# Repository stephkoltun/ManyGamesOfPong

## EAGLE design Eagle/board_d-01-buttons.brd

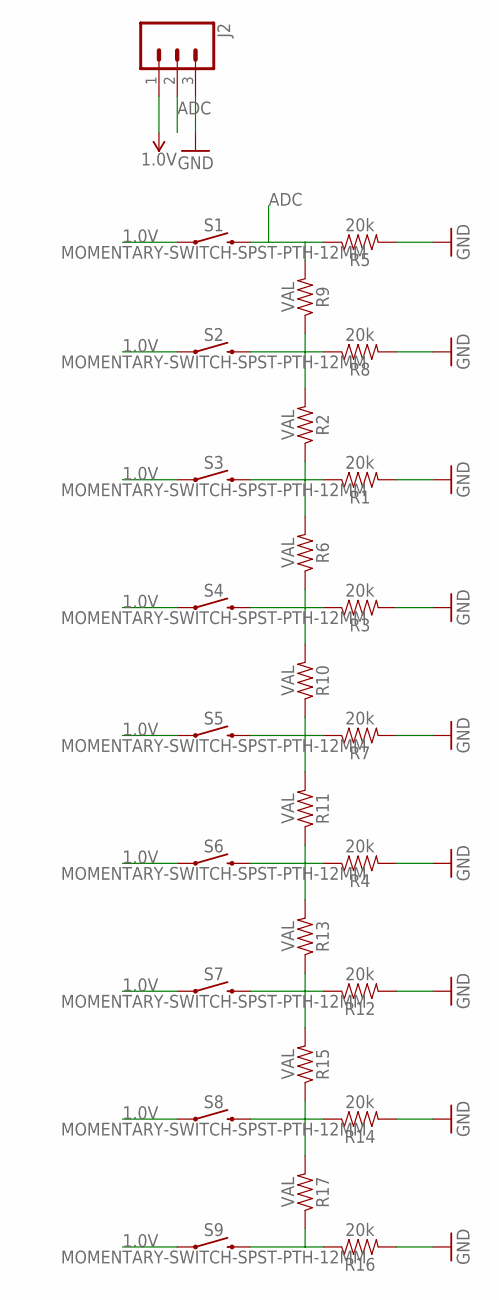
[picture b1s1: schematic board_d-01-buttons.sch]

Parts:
J2: CONN_03LOCK_LONGPADS; 1X03_LOCK_LONGPADS
R1, R3, R4, R5, R7, R8, R12, R14, R16: 20k; AXIAL-0.3
R2, R6, R9, R10, R11, R13, R15, R17: VAL; AXIAL-0.3
S1, S2, S3, S4, S5, S6, S7, S8, S9: MOMENTARY-SWITCH-SPST-PTH-12MM; TACTILE_SWITCH_PTH_12MM

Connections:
1.0V: J2.1, S1.1, S2.1, S3.1, S4.1, S5.1, S6.1, S7.1, S8.1, S9.1
ADC: J2.2, R5.P$1 (1), R9.P$2 (2), S1.3 (2)
GND: J2.3, R1.P$2 (2), R3.P$2 (2), R4.P$2 (2), R5.P$2 (2), R7.P$2 (2), R8.P$2 (2), R12.P$2 (2), R14.P$2 (2), R16.P$2 (2)
unnamed: R1.P$1 (1), R2.P$1 (1), R6.P$2 (2), S3.3 (2)
unnamed: R3.P$1 (1), R6.P$1 (1), R10.P$2 (2), S4.3 (2)
unnamed: R7.P$1 (1), R10.P$1 (1), R11.P$2 (2), S5.3 (2)
unnamed: R4.P$1 (1), R11.P$1 (1), R13.P$2 (2), S6.3 (2)
unnamed: R2.P$2 (2), R8.P$1 (1), R9.P$1 (1), S2.3 (2)
unnamed: R12.P$1 (1), R13.P$1 (1), R15.P$2 (2), S7.3 (2)
unnamed: R14.P$1 (1), R15.P$1 (1), R17.P$2 (2), S8.3 (2)
unnamed: R16.P$1 (1), R17.P$1 (1), S9.3 (2)

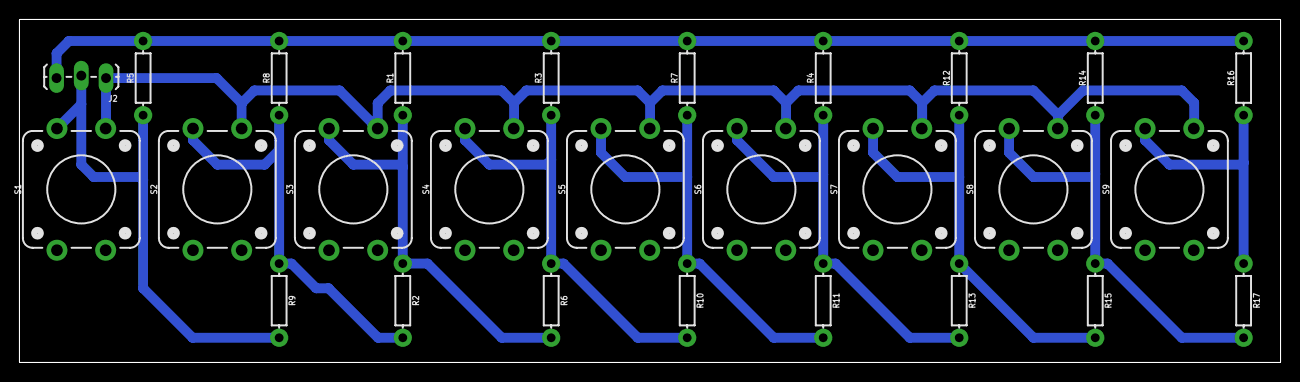
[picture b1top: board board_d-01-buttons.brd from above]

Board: 2 copper layers, 129.5 x 35.2 mm, 27 parts (0 on the bottom side), 11 nets.

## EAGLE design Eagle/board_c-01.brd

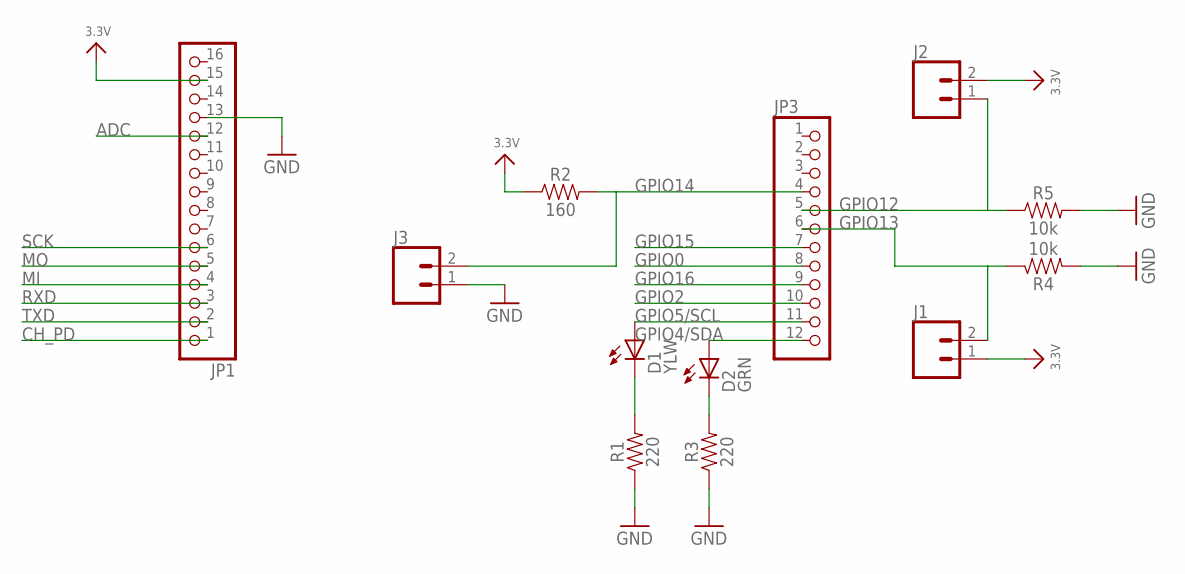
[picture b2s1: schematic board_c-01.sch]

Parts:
D1: YLW; LED3MM
D2: GRN; LED3MM
J1, J2, J3: CONN_02LOCK_LONGPADS; 1X02_LOCK_LONGPADS
JP1: HEADER-1X16ROUND; 1X16_ROUND
JP3: HEADER-1X12; 1X12_ROUND
R1, R3: 220; AXIAL-0.3
R2: 160; AXIAL-0.3
R4, R5: 10k; AXIAL-0.3

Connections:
3.3V: J1.1, J2.2, JP1.15, R2.P$1 (1)
ADC: JP1.12
CH_PD: JP1.1
GND: J3.1, JP1.13, R1.P$1 (1), R3.P$1 (1), R4.P$2 (2), R5.P$2 (2)
GPIO0: JP3.8
GPIO2: JP3.10
GPIO4/SDA: D2.A, JP3.12
GPIO5/SCL: D1.A, JP3.11
GPIO12: J2.1, JP3.5, R5.P$1 (1)
GPIO13: J1.2, JP3.6, R4.P$1 (1)
GPIO14: J3.2, JP3.4, R2.P$2 (2)
GPIO15: JP3.7
GPIO16: JP3.9
MI: JP1.4
MO: JP1.5
unnamed: D1.K (C), R1.P$2 (2)
unnamed: D2.K (C), R3.P$2 (2)
RXD: JP1.3
SCK: JP1.6
TXD: JP1.2

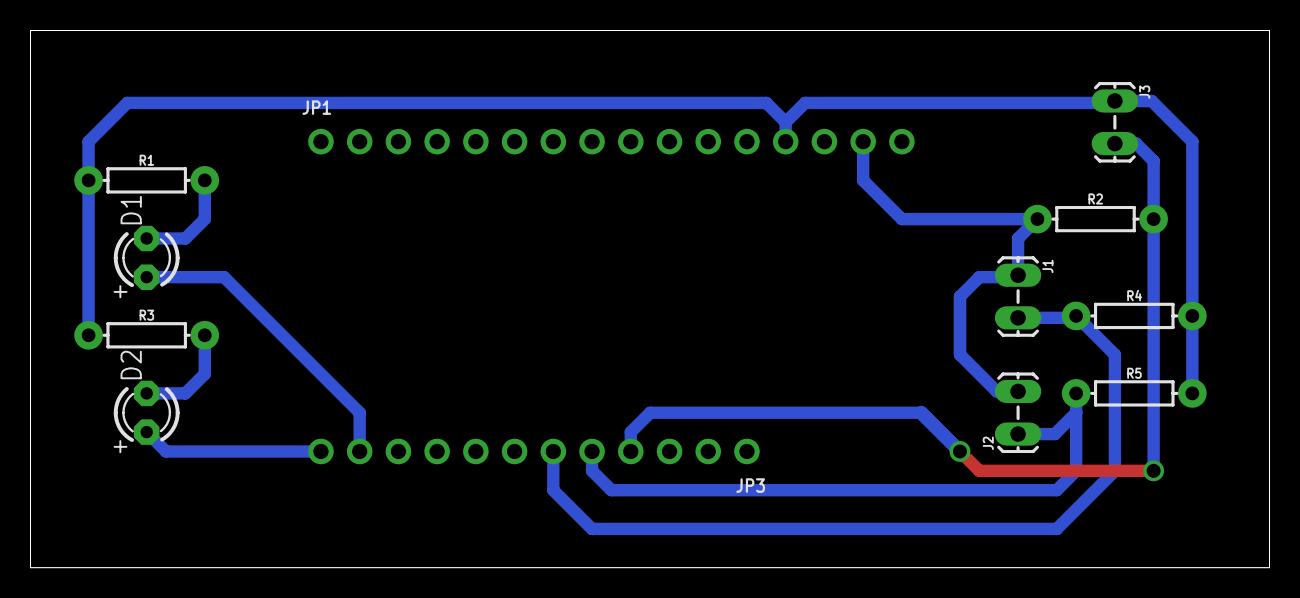
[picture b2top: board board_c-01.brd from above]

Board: 2 copper layers, 81.3 x 35.2 mm, 12 parts (0 on the bottom side), 9 nets.

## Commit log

2017-03-10 updated to ESP8266 chip
2018-02-10 updated to most recent controllers
2018-02-10 renamed files

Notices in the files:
parts and their libraries:
SparkFun-Connectors: Licensing: Creative Commons ShareAlike 4.0 International - https://creativecommons.org/licenses/by-sa/4.0
microbuilder: This work is placed in the public domain, and may be freely used for commercial and non-commercial work with the following conditions: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
